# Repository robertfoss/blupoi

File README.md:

blupoi
======

TODO
----

Changes since v0.3:
 - 1uF 0402 caps not ordered
 * C27 pad has a large via in a pad
 * FIXED: MAX16054 Connect CLEAR to GND if unused.
 * FIXED: SIP32408 Footprint pinout was mirrored
 ? Change battery orientation, since spring should be on the top side but also on the gnd side of BAT
  - Maybe dont since VBAT would end up coming out in a place where it is not useful
 * X1 label covered by hole
 * X1 footprint larger than bom part?
 * C1/C2/C3 footprint is 0603 but bom is 0402
 * SWO header, change part and footprint to have only be connectable the 'right' way

Changes since v0.2:
 * FIXED: Replaced USB connector oval holes with round ones for improved fabricability
 * FIXED: Reflowed filled zones since KiCad somehow did it randomly wrong in v0.2
 * FIXED: R1 Move via further away from pad
 * FIXED: Move USB connector and power button to the side

Changes since v0.1:
 * FIXED: Battery compartment is not quite wide enough.
 * IGNORE: Battery compartment battery spring slot is:
   - 0.5mm too thin, should be 1.6mm
   - 0.5mm too slim, should me 17.75mm
 * FIXED: Spring slots lack copper on the back side
 * FIXED: +/- symbols on the battery silkscreen
 ? IGNORE: battery footprint 180 degrees

 * FIXED: U5/bq24075 EN1 is not pulled down
 * FIXED: U5/bq24075 sysoff turns charging off. Which is should never dd
   - Add separate add some kind of switch between u5 out and vin, controlled by button logic
   - Pull sysoff down
 * Add Load switch like Sip32431 - http://www.vishay.com/docs/66597/sip32431.pdf
   - But ~4.8A at @ 5V
   - SiP32101? No. Is LGA package
   - SiP32408? 3.5A probably ok since no usb port delivers that, and probable no battery either
     - http://www.vishay.com/docs/63717/sip32408.pdf

 * FIXED: Mic port hole is not drilled (hole too small?)
 * FIXED: Mic pads should probably be longer

 * FIXED: Move button footprint slightly closer to edge

 * FIXED: BNO055 pads should probable be longer

 * FIXED: Make logos bigger to make details visible

 * FIXED: Change L2 footprint from 0603 to 1206

 * Vin not connected on 3.3V regulator

 * FIXED: Add silkscreen saying:
   look at you, hacker, a pathetic creature of meat and bone. how can you compare yourself to a perfect immortal machine.

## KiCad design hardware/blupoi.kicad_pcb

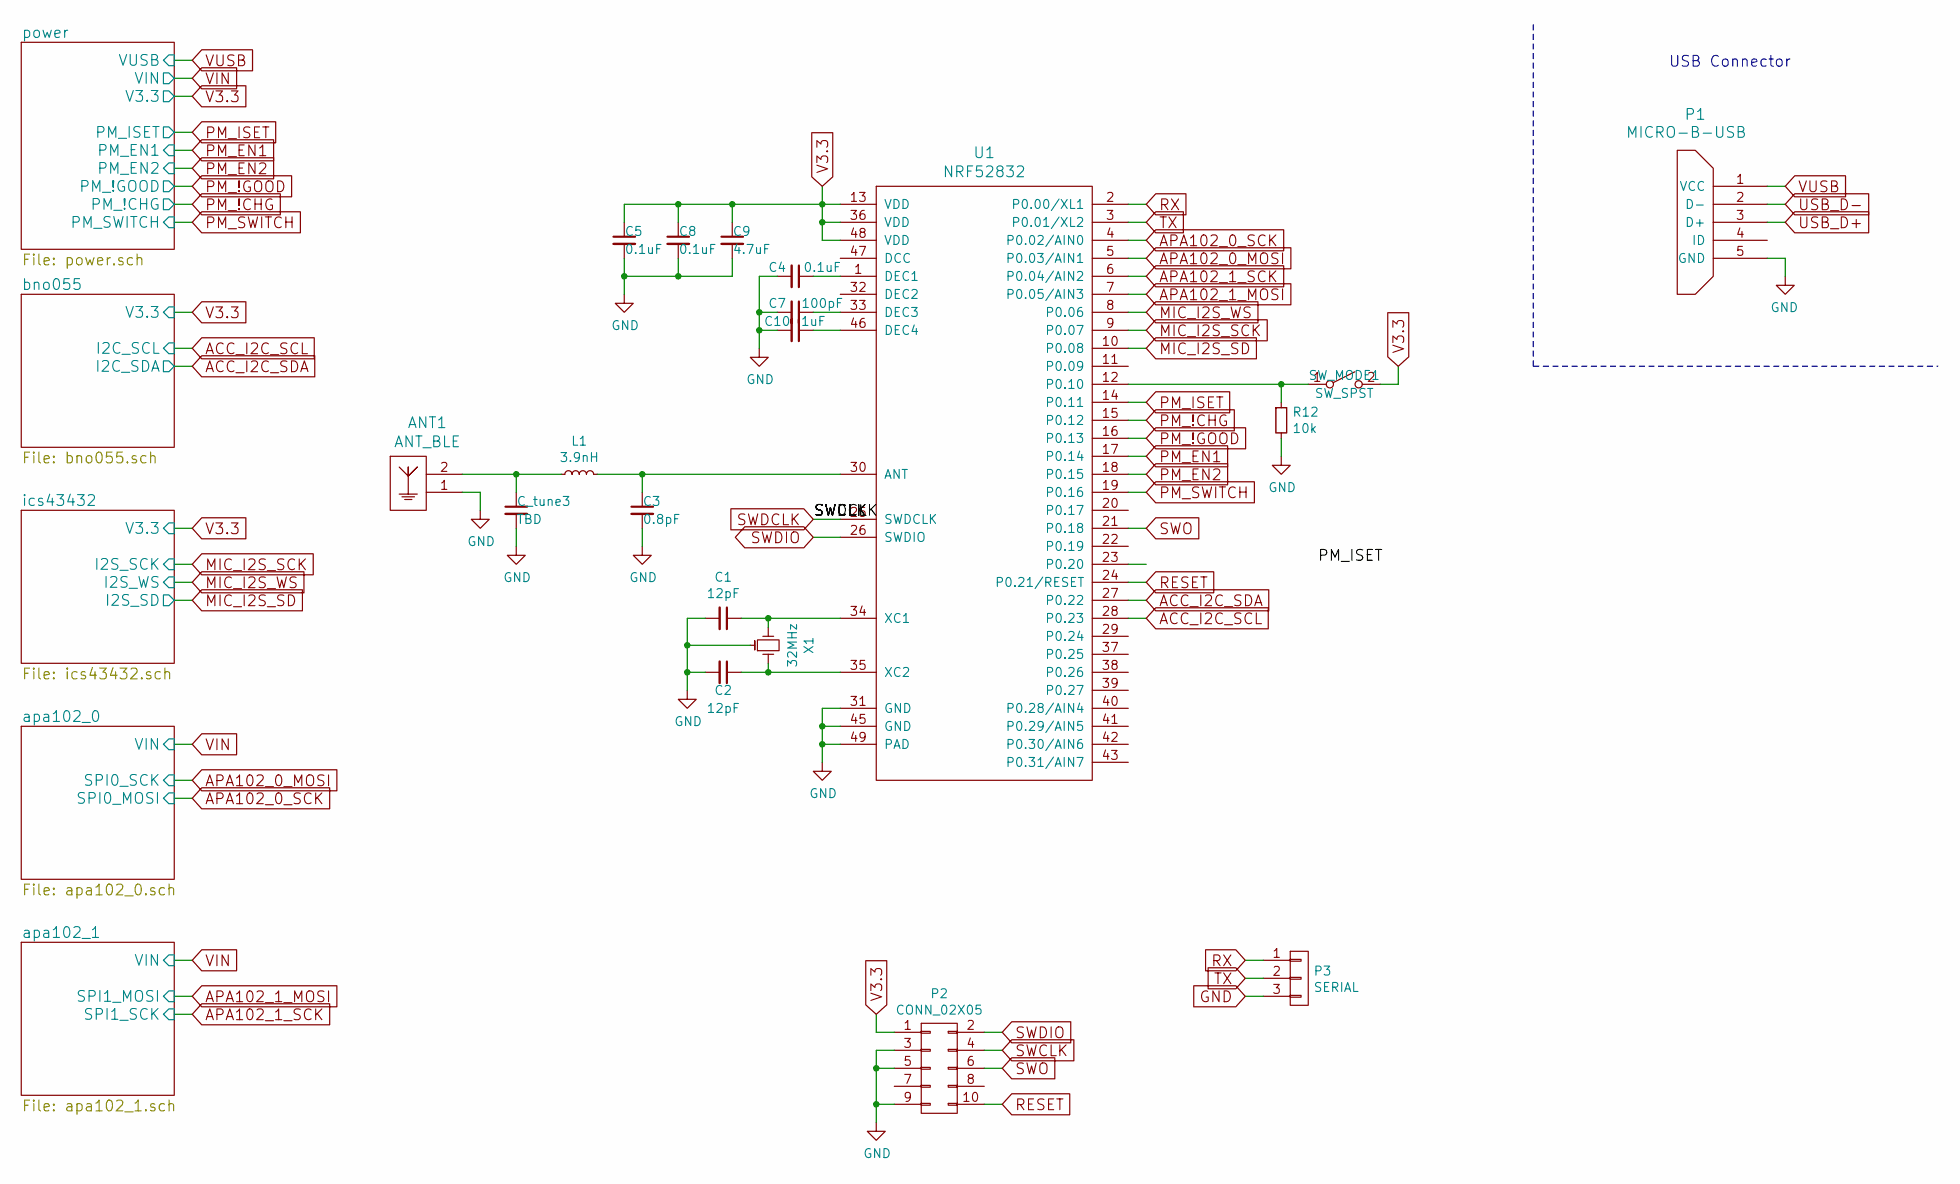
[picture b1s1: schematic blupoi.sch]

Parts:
ANT1: ANT_BLE; ti-an043-antenna
C1, C2: 12pF; C_0402
C3: 0.8pF; C_0402; MFG Part Num Value
C4: 0.1uF; C_0402
C5, C8: 0.1uF; C_0402; MFG Part Num Value
C7: 100pF; C_0402; MFG Part Num Value
C9: 4.7uF; C_0603; MFG Part Num Value
C10: 1uF; C_0603; MFG Part Num Value
C_tune3: TBD; C_0603_HandSoldering; MFG Part Num Value
L1: 3.9nH; C_0402
P1: MICRO-B-USB; USB_Micro-B
P2: CONN_02X05; Pin_Header_Straight_2x05
P3: SERIAL; Pin_Header_Straight_1x03
R12: 10k; R_0603
SW_MODE1: SW_SPST; KSS241GLFS
U1: NRF52832; UQFN-48-1EP_6x6mm_Pitch0.4mm
X1: 32MHz; XTAL2016; MFG Part Num Value

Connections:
ACC_I2C_SCL: U1.28 (P0.23); also elsewhere on the board
ACC_I2C_SDA: U1.27 (P0.22); also elsewhere on the board
APA102_0_MOSI: U1.5 (P0.03/AIN1); also elsewhere on the board
APA102_0_SCK: U1.4 (P0.02/AIN0); also elsewhere on the board
APA102_1_MOSI: U1.7 (P0.05/AIN3); also elsewhere on the board
APA102_1_SCK: U1.6 (P0.04/AIN2); also elsewhere on the board
GND: ANT1.1, C1.2, C2.2, C3.2, C4.2, C5.2, C7.2, C8.2, C9.2, C10.2, C_tune3.2, P1.5 (GND), P2.3, P2.5, P2.9, R12.2, U1.31 (GND), U1.45 (GND), U1.49 (PAD), X1.3; also elsewhere on the board
MIC_I2S_SCK: U1.9 (P0.07); also elsewhere on the board
MIC_I2S_SD: U1.10 (P0.08); also elsewhere on the board
MIC_I2S_WS: U1.8 (P0.06); also elsewhere on the board
unnamed: ANT1.2, C_tune3.1, L1.1
unnamed: C1.1, U1.34 (XC1), X1.2
unnamed: C2.1, U1.35 (XC2), X1.1
unnamed: C3.1, L1.2, U1.30 (ANT)
unnamed: C4.1, U1.1 (DEC1)
unnamed: C7.1, U1.33 (DEC3)
unnamed: C10.1, U1.46 (DEC4)
unnamed: R12.1, SW_MODE1.1 (A), U1.12 (P0.10)
PM_!CHG: U1.15 (P0.12); also elsewhere on the board
PM_!GOOD: U1.16 (P0.13); also elsewhere on the board
PM_EN1: U1.17 (P0.14); also elsewhere on the board
PM_EN2: U1.18 (P0.15); also elsewhere on the board
PM_ISET: U1.14 (P0.11); also elsewhere on the board
PM_SWITCH: U1.19 (P0.16); also elsewhere on the board
RESET: P2.10, U1.24 (P0.21/RESET); also elsewhere on the board
RX: P3.1, U1.2 (P0.00/XL1); also elsewhere on the board
SWCLK: U1.25 (SWDCLK); also elsewhere on the board
SWDIO: P2.2, U1.26 (SWDIO); also elsewhere on the board
SWO: P2.6, U1.21 (P0.18); also elsewhere on the board
TX: P3.2, U1.3 (P0.01/XL2); also elsewhere on the board
USB_D+: P1.3 (D+)
USB_D-: P1.2 (D-)
V3.3: C5.1, C8.1, C9.1, P2.1, SW_MODE1.2 (B), U1.13 (VDD), U1.36 (VDD), U1.48 (VDD); also elsewhere on the board
VUSB: P1.1 (VCC); also elsewhere on the board

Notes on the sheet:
USB Connector

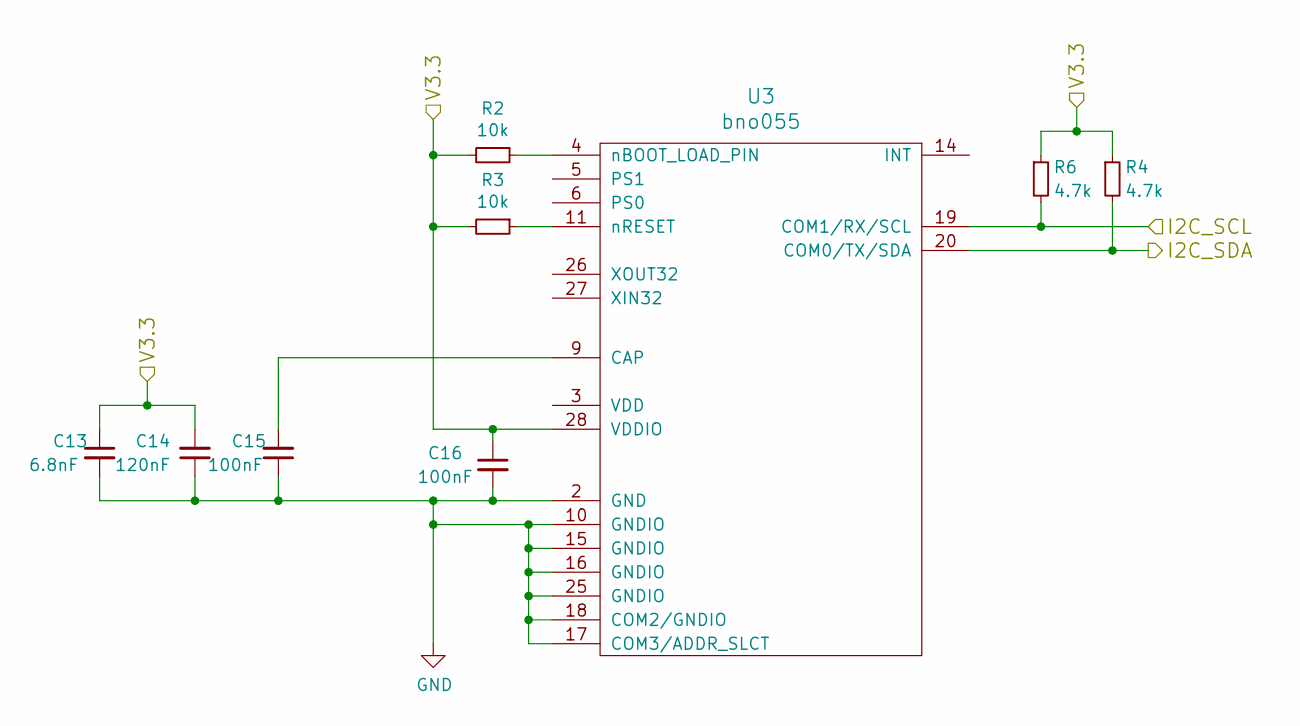
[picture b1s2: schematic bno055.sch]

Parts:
C13: 6.8nF; C_0402
C14: 120nF; C_0402
C15, C16: 100nF; C_0402
R2, R3: 10k; R_0603
R4, R6: 4.7k; R_0603
U3: bno055

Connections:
ACC_I2C_SCL: R6.2, U3.19 (COM1/RX/SCL); also elsewhere on the board
ACC_I2C_SDA: R4.2, U3.20 (COM0/TX/SDA); also elsewhere on the board
GND: C13.2, C14.1, C15.1, C16.2, U3.2 (GND), U3.10 (GNDIO), U3.15 (GNDIO), U3.16 (GNDIO), U3.17 (COM3/ADDR_SLCT), U3.18 (COM2/GNDIO), U3.25 (GNDIO); also elsewhere on the board
unnamed: C15.2, U3.9 (CAP)
unnamed: R2.1, U3.4 (nBOOT_LOAD_PIN)
unnamed: R3.1, U3.11 (nRESET)
V3.3: C13.1, C14.2, C16.1, R2.2, R3.2, R4.1, R6.1, U3.28 (VDDIO); also elsewhere on the board

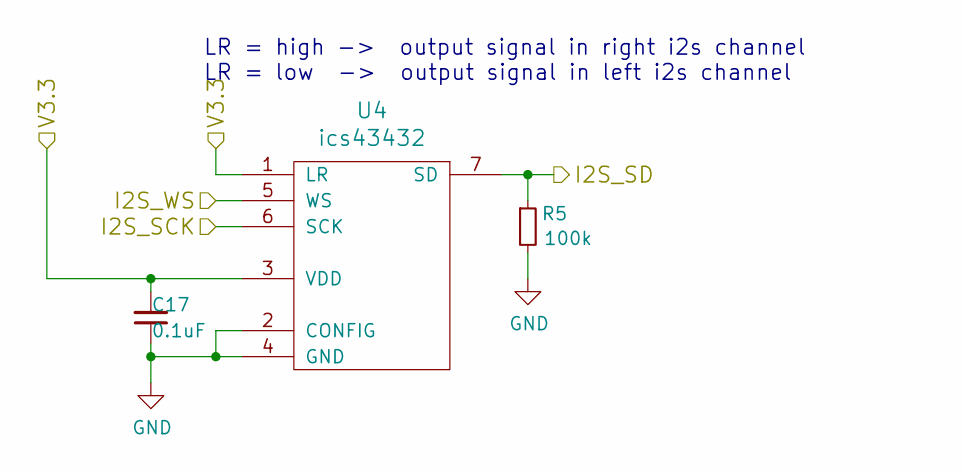
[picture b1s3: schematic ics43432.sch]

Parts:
C17: 0.1uF; C_0402
R5: 100k; R_0603
U4: ics43432

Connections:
GND: C17.1, R5.2, U4.2 (CONFIG), U4.4 (GND); also elsewhere on the board
MIC_I2S_SCK: U4.6 (SCK); also elsewhere on the board
MIC_I2S_SD: R5.1, U4.7 (SD); also elsewhere on the board
MIC_I2S_WS: U4.5 (WS); also elsewhere on the board
V3.3: C17.2, U4.1 (LR), U4.3 (VDD); also elsewhere on the board

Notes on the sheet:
LR = high -> output signal in right i2s channel LR = low -> output signal in left i2s channel

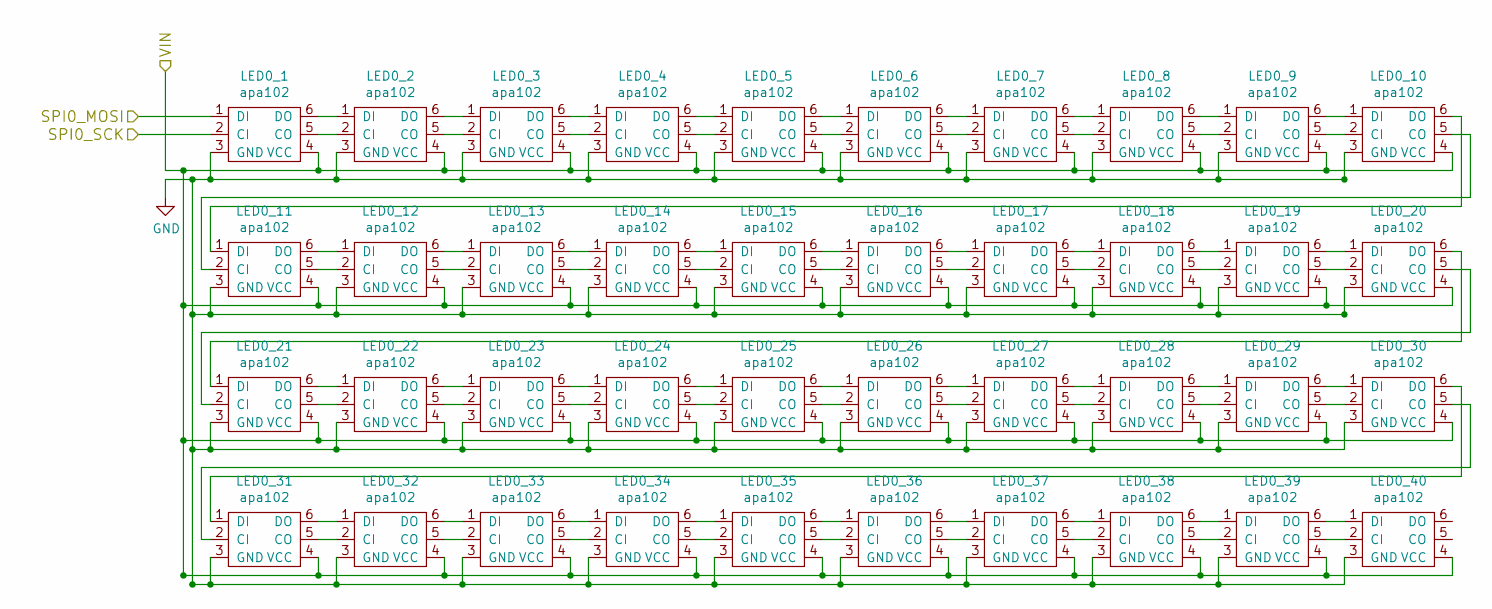
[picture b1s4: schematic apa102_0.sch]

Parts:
LED0_1, LED0_2, LED0_3, LED0_4, LED0_5, LED0_6, LED0_7, LED0_8, LED0_9, LED0_10, LED0_11, LED0_12, LED0_13, LED0_14, LED0_15, LED0_16, LED0_17, LED0_18, LED0_19, LED0_20, LED0_21, LED0_22, LED0_23, LED0_24, LED0_25, LED0_26, LED0_27, LED0_28, LED0_29, LED0_30, LED0_31, LED0_32, LED0_33, LED0_34, LED0_35, LED0_36, LED0_37, LED0_38, LED0_39, LED0_40: apa102

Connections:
APA102_0_MOSI: LED0_1.2 (CI); also elsewhere on the board
APA102_0_SCK: LED0_1.1 (DI); also elsewhere on the board
GND: LED0_1.3 (GND), LED0_2.3 (GND), LED0_3.3 (GND), LED0_4.3 (GND), LED0_5.3 (GND), LED0_6.3 (GND), LED0_7.3 (GND), LED0_8.3 (GND), LED0_9.3 (GND), LED0_10.3 (GND), LED0_11.3 (GND), LED0_12.3 (GND), LED0_13.3 (GND), LED0_14.3 (GND), LED0_15.3 (GND), LED0_16.3 (GND), LED0_17.3 (GND), LED0_18.3 (GND), LED0_19.3 (GND), LED0_20.3 (GND), LED0_21.3 (GND), LED0_22.3 (GND), LED0_23.3 (GND), LED0_24.3 (GND), LED0_25.3 (GND), LED0_26.3 (GND), LED0_27.3 (GND), LED0_28.3 (GND), LED0_29.3 (GND), LED0_30.3 (GND), LED0_31.3 (GND), LED0_32.3 (GND), LED0_33.3 (GND), LED0_34.3 (GND), LED0_35.3 (GND), LED0_36.3 (GND), LED0_37.3 (GND), LED0_38.3 (GND), LED0_39.3 (GND), LED0_40.3 (GND); also elsewhere on the board
unnamed: LED0_1.5 (CO), LED0_2.2 (CI)
unnamed: LED0_1.6 (DO), LED0_2.1 (DI)
unnamed: LED0_2.5 (CO), LED0_3.2 (CI)
unnamed: LED0_2.6 (DO), LED0_3.1 (DI)
unnamed: LED0_3.5 (CO), LED0_4.2 (CI)
unnamed: LED0_3.6 (DO), LED0_4.1 (DI)
unnamed: LED0_4.5 (CO), LED0_5.2 (CI)
unnamed: LED0_4.6 (DO), LED0_5.1 (DI)
unnamed: LED0_5.5 (CO), LED0_6.2 (CI)
unnamed: LED0_5.6 (DO), LED0_6.1 (DI)
unnamed: LED0_6.5 (CO), LED0_7.2 (CI)
unnamed: LED0_6.6 (DO), LED0_7.1 (DI)
unnamed: LED0_7.5 (CO), LED0_8.2 (CI)
unnamed: LED0_7.6 (DO), LED0_8.1 (DI)
unnamed: LED0_8.5 (CO), LED0_9.2 (CI)
unnamed: LED0_8.6 (DO), LED0_9.1 (DI)
unnamed: LED0_9.6 (DO), LED0_10.1 (DI)
unnamed: LED0_9.5 (CO), LED0_10.2 (CI)
unnamed: LED0_10.5 (CO), LED0_11.2 (CI)
unnamed: LED0_10.6 (DO), LED0_11.1 (DI)
unnamed: LED0_11.5 (CO), LED0_12.2 (CI)
unnamed: LED0_11.6 (DO), LED0_12.1 (DI)
unnamed: LED0_12.5 (CO), LED0_13.2 (CI)
unnamed: LED0_12.6 (DO), LED0_13.1 (DI)
unnamed: LED0_13.5 (CO), LED0_14.2 (CI)
unnamed: LED0_13.6 (DO), LED0_14.1 (DI)
unnamed: LED0_14.5 (CO), LED0_15.2 (CI)
unnamed: LED0_14.6 (DO), LED0_15.1 (DI)
unnamed: LED0_15.5 (CO), LED0_16.2 (CI)
unnamed: LED0_15.6 (DO), LED0_16.1 (DI)
unnamed: LED0_16.5 (CO), LED0_17.2 (CI)
unnamed: LED0_16.6 (DO), LED0_17.1 (DI)
unnamed: LED0_17.5 (CO), LED0_18.2 (CI)
unnamed: LED0_17.6 (DO), LED0_18.1 (DI)
unnamed: LED0_18.5 (CO), LED0_19.2 (CI)
unnamed: LED0_18.6 (DO), LED0_19.1 (DI)
unnamed: LED0_19.5 (CO), LED0_20.2 (CI)
unnamed: LED0_19.6 (DO), LED0_20.1 (DI)
unnamed: LED0_20.5 (CO), LED0_21.2 (CI)
unnamed: LED0_20.6 (DO), LED0_21.1 (DI)
unnamed: LED0_21.5 (CO), LED0_22.2 (CI)
unnamed: LED0_21.6 (DO), LED0_22.1 (DI)
unnamed: LED0_22.5 (CO), LED0_23.2 (CI)
unnamed: LED0_22.6 (DO), LED0_23.1 (DI)
unnamed: LED0_23.5 (CO), LED0_24.2 (CI)
unnamed: LED0_23.6 (DO), LED0_24.1 (DI)
unnamed: LED0_24.5 (CO), LED0_25.2 (CI)
unnamed: LED0_24.6 (DO), LED0_25.1 (DI)
unnamed: LED0_25.5 (CO), LED0_26.2 (CI)
unnamed: LED0_25.6 (DO), LED0_26.1 (DI)
unnamed: LED0_26.5 (CO), LED0_27.2 (CI)
unnamed: LED0_26.6 (DO), LED0_27.1 (DI)
unnamed: LED0_27.5 (CO), LED0_28.2 (CI)
unnamed: LED0_27.6 (DO), LED0_28.1 (DI)
unnamed: LED0_28.5 (CO), LED0_29.2 (CI)
unnamed: LED0_28.6 (DO), LED0_29.1 (DI)
unnamed: LED0_29.5 (CO), LED0_30.2 (CI)
unnamed: LED0_29.6 (DO), LED0_30.1 (DI)
unnamed: LED0_30.5 (CO), LED0_31.2 (CI)
unnamed: LED0_30.6 (DO), LED0_31.1 (DI)
unnamed: LED0_31.5 (CO), LED0_32.2 (CI)
unnamed: LED0_31.6 (DO), LED0_32.1 (DI)
unnamed: LED0_32.5 (CO), LED0_33.2 (CI)
unnamed: LED0_32.6 (DO), LED0_33.1 (DI)
unnamed: LED0_33.5 (CO), LED0_34.2 (CI)
unnamed: LED0_33.6 (DO), LED0_34.1 (DI)
unnamed: LED0_34.5 (CO), LED0_35.2 (CI)
unnamed: LED0_34.6 (DO), LED0_35.1 (DI)
unnamed: LED0_35.5 (CO), LED0_36.2 (CI)
unnamed: LED0_35.6 (DO), LED0_36.1 (DI)
unnamed: LED0_36.5 (CO), LED0_37.2 (CI)
unnamed: LED0_36.6 (DO), LED0_37.1 (DI)
unnamed: LED0_37.5 (CO), LED0_38.2 (CI)
unnamed: LED0_37.6 (DO), LED0_38.1 (DI)
unnamed: LED0_38.5 (CO), LED0_39.2 (CI)
unnamed: LED0_38.6 (DO), LED0_39.1 (DI)
unnamed: LED0_39.5 (CO), LED0_40.2 (CI)
unnamed: LED0_39.6 (DO), LED0_40.1 (DI)
VIN: LED0_1.4 (VCC), LED0_2.4 (VCC), LED0_3.4 (VCC), LED0_4.4 (VCC), LED0_5.4 (VCC), LED0_6.4 (VCC), LED0_7.4 (VCC), LED0_8.4 (VCC), LED0_9.4 (VCC), LED0_10.4 (VCC), LED0_11.4 (VCC), LED0_12.4 (VCC), LED0_13.4 (VCC), LED0_14.4 (VCC), LED0_15.4 (VCC), LED0_16.4 (VCC), LED0_17.4 (VCC), LED0_18.4 (VCC), LED0_19.4 (VCC), LED0_20.4 (VCC), LED0_21.4 (VCC), LED0_22.4 (VCC), LED0_23.4 (VCC), LED0_24.4 (VCC), LED0_25.4 (VCC), LED0_26.4 (VCC), LED0_27.4 (VCC), LED0_28.4 (VCC), LED0_29.4 (VCC), LED0_30.4 (VCC), LED0_31.4 (VCC), LED0_32.4 (VCC), LED0_33.4 (VCC), LED0_34.4 (VCC), LED0_35.4 (VCC), LED0_36.4 (VCC), LED0_37.4 (VCC), LED0_38.4 (VCC), LED0_39.4 (VCC), LED0_40.4 (VCC); also elsewhere on the board

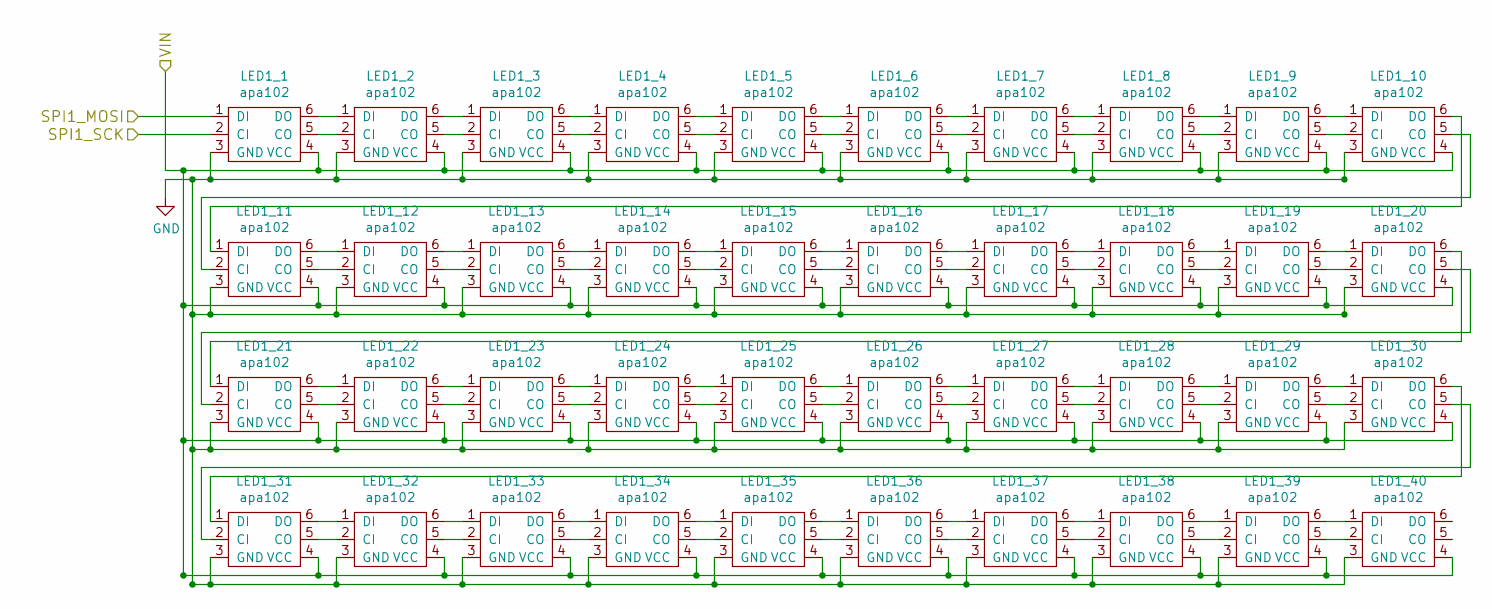
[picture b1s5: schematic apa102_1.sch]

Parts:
LED1_1, LED1_2, LED1_3, LED1_4, LED1_5, LED1_6, LED1_7, LED1_8, LED1_9, LED1_10, LED1_11, LED1_12, LED1_13, LED1_14, LED1_15, LED1_16, LED1_17, LED1_18, LED1_19, LED1_20, LED1_21, LED1_22, LED1_23, LED1_24, LED1_25, LED1_26, LED1_27, LED1_28, LED1_29, LED1_30, LED1_31, LED1_32, LED1_33, LED1_34, LED1_35, LED1_36, LED1_37, LED1_38, LED1_39, LED1_40: apa102

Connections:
APA102_1_MOSI: LED1_1.1 (DI); also elsewhere on the board
APA102_1_SCK: LED1_1.2 (CI); also elsewhere on the board
GND: LED1_1.3 (GND), LED1_2.3 (GND), LED1_3.3 (GND), LED1_4.3 (GND), LED1_5.3 (GND), LED1_6.3 (GND), LED1_7.3 (GND), LED1_8.3 (GND), LED1_9.3 (GND), LED1_10.3 (GND), LED1_11.3 (GND), LED1_12.3 (GND), LED1_13.3 (GND), LED1_14.3 (GND), LED1_15.3 (GND), LED1_16.3 (GND), LED1_17.3 (GND), LED1_18.3 (GND), LED1_19.3 (GND), LED1_20.3 (GND), LED1_21.3 (GND), LED1_22.3 (GND), LED1_23.3 (GND), LED1_24.3 (GND), LED1_25.3 (GND), LED1_26.3 (GND), LED1_27.3 (GND), LED1_28.3 (GND), LED1_29.3 (GND), LED1_30.3 (GND), LED1_31.3 (GND), LED1_32.3 (GND), LED1_33.3 (GND), LED1_34.3 (GND), LED1_35.3 (GND), LED1_36.3 (GND), LED1_37.3 (GND), LED1_38.3 (GND), LED1_39.3 (GND), LED1_40.3 (GND); also elsewhere on the board
unnamed: LED1_1.5 (CO), LED1_2.2 (CI)
unnamed: LED1_1.6 (DO), LED1_2.1 (DI)
unnamed: LED1_2.5 (CO), LED1_3.2 (CI)
unnamed: LED1_2.6 (DO), LED1_3.1 (DI)
unnamed: LED1_3.5 (CO), LED1_4.2 (CI)
unnamed: LED1_3.6 (DO), LED1_4.1 (DI)
unnamed: LED1_4.5 (CO), LED1_5.2 (CI)
unnamed: LED1_4.6 (DO), LED1_5.1 (DI)
unnamed: LED1_5.5 (CO), LED1_6.2 (CI)
unnamed: LED1_5.6 (DO), LED1_6.1 (DI)
unnamed: LED1_6.5 (CO), LED1_7.2 (CI)
unnamed: LED1_6.6 (DO), LED1_7.1 (DI)
unnamed: LED1_7.5 (CO), LED1_8.2 (CI)
unnamed: LED1_7.6 (DO), LED1_8.1 (DI)
unnamed: LED1_8.5 (CO), LED1_9.2 (CI)
unnamed: LED1_8.6 (DO), LED1_9.1 (DI)
unnamed: LED1_9.6 (DO), LED1_10.1 (DI)
unnamed: LED1_9.5 (CO), LED1_10.2 (CI)
unnamed: LED1_10.5 (CO), LED1_11.2 (CI)
unnamed: LED1_10.6 (DO), LED1_11.1 (DI)
unnamed: LED1_11.5 (CO), LED1_12.2 (CI)
unnamed: LED1_11.6 (DO), LED1_12.1 (DI)
unnamed: LED1_12.5 (CO), LED1_13.2 (CI)
unnamed: LED1_12.6 (DO), LED1_13.1 (DI)
unnamed: LED1_13.5 (CO), LED1_14.2 (CI)
unnamed: LED1_13.6 (DO), LED1_14.1 (DI)
unnamed: LED1_14.5 (CO), LED1_15.2 (CI)
unnamed: LED1_14.6 (DO), LED1_15.1 (DI)
unnamed: LED1_15.5 (CO), LED1_16.2 (CI)
unnamed: LED1_15.6 (DO), LED1_16.1 (DI)
unnamed: LED1_16.5 (CO), LED1_17.2 (CI)
unnamed: LED1_16.6 (DO), LED1_17.1 (DI)
unnamed: LED1_17.5 (CO), LED1_18.2 (CI)
unnamed: LED1_17.6 (DO), LED1_18.1 (DI)
unnamed: LED1_18.5 (CO), LED1_19.2 (CI)
unnamed: LED1_18.6 (DO), LED1_19.1 (DI)
unnamed: LED1_19.5 (CO), LED1_20.2 (CI)
unnamed: LED1_19.6 (DO), LED1_20.1 (DI)
unnamed: LED1_20.5 (CO), LED1_21.2 (CI)
unnamed: LED1_20.6 (DO), LED1_21.1 (DI)
unnamed: LED1_21.5 (CO), LED1_22.2 (CI)
unnamed: LED1_21.6 (DO), LED1_22.1 (DI)
unnamed: LED1_22.5 (CO), LED1_23.2 (CI)
unnamed: LED1_22.6 (DO), LED1_23.1 (DI)
unnamed: LED1_23.5 (CO), LED1_24.2 (CI)
unnamed: LED1_23.6 (DO), LED1_24.1 (DI)
unnamed: LED1_24.5 (CO), LED1_25.2 (CI)
unnamed: LED1_24.6 (DO), LED1_25.1 (DI)
unnamed: LED1_25.5 (CO), LED1_26.2 (CI)
unnamed: LED1_25.6 (DO), LED1_26.1 (DI)
unnamed: LED1_26.5 (CO), LED1_27.2 (CI)
unnamed: LED1_26.6 (DO), LED1_27.1 (DI)
unnamed: LED1_27.5 (CO), LED1_28.2 (CI)
unnamed: LED1_27.6 (DO), LED1_28.1 (DI)
unnamed: LED1_28.5 (CO), LED1_29.2 (CI)
unnamed: LED1_28.6 (DO), LED1_29.1 (DI)
unnamed: LED1_29.5 (CO), LED1_30.2 (CI)
unnamed: LED1_29.6 (DO), LED1_30.1 (DI)
unnamed: LED1_30.5 (CO), LED1_31.2 (CI)
unnamed: LED1_30.6 (DO), LED1_31.1 (DI)
unnamed: LED1_31.5 (CO), LED1_32.2 (CI)
unnamed: LED1_31.6 (DO), LED1_32.1 (DI)
unnamed: LED1_32.5 (CO), LED1_33.2 (CI)
unnamed: LED1_32.6 (DO), LED1_33.1 (DI)
unnamed: LED1_33.5 (CO), LED1_34.2 (CI)
unnamed: LED1_33.6 (DO), LED1_34.1 (DI)
unnamed: LED1_34.5 (CO), LED1_35.2 (CI)
unnamed: LED1_34.6 (DO), LED1_35.1 (DI)
unnamed: LED1_35.5 (CO), LED1_36.2 (CI)
unnamed: LED1_35.6 (DO), LED1_36.1 (DI)
unnamed: LED1_36.5 (CO), LED1_37.2 (CI)
unnamed: LED1_36.6 (DO), LED1_37.1 (DI)
unnamed: LED1_37.5 (CO), LED1_38.2 (CI)
unnamed: LED1_37.6 (DO), LED1_38.1 (DI)
unnamed: LED1_38.5 (CO), LED1_39.2 (CI)
unnamed: LED1_38.6 (DO), LED1_39.1 (DI)
unnamed: LED1_39.5 (CO), LED1_40.2 (CI)
unnamed: LED1_39.6 (DO), LED1_40.1 (DI)
VIN: LED1_1.4 (VCC), LED1_2.4 (VCC), LED1_3.4 (VCC), LED1_4.4 (VCC), LED1_5.4 (VCC), LED1_6.4 (VCC), LED1_7.4 (VCC), LED1_8.4 (VCC), LED1_9.4 (VCC), LED1_10.4 (VCC), LED1_11.4 (VCC), LED1_12.4 (VCC), LED1_13.4 (VCC), LED1_14.4 (VCC), LED1_15.4 (VCC), LED1_16.4 (VCC), LED1_17.4 (VCC), LED1_18.4 (VCC), LED1_19.4 (VCC), LED1_20.4 (VCC), LED1_21.4 (VCC), LED1_22.4 (VCC), LED1_23.4 (VCC), LED1_24.4 (VCC), LED1_25.4 (VCC), LED1_26.4 (VCC), LED1_27.4 (VCC), LED1_28.4 (VCC), LED1_29.4 (VCC), LED1_30.4 (VCC), LED1_31.4 (VCC), LED1_32.4 (VCC), LED1_33.4 (VCC), LED1_34.4 (VCC), LED1_35.4 (VCC), LED1_36.4 (VCC), LED1_37.4 (VCC), LED1_38.4 (VCC), LED1_39.4 (VCC), LED1_40.4 (VCC); also elsewhere on the board

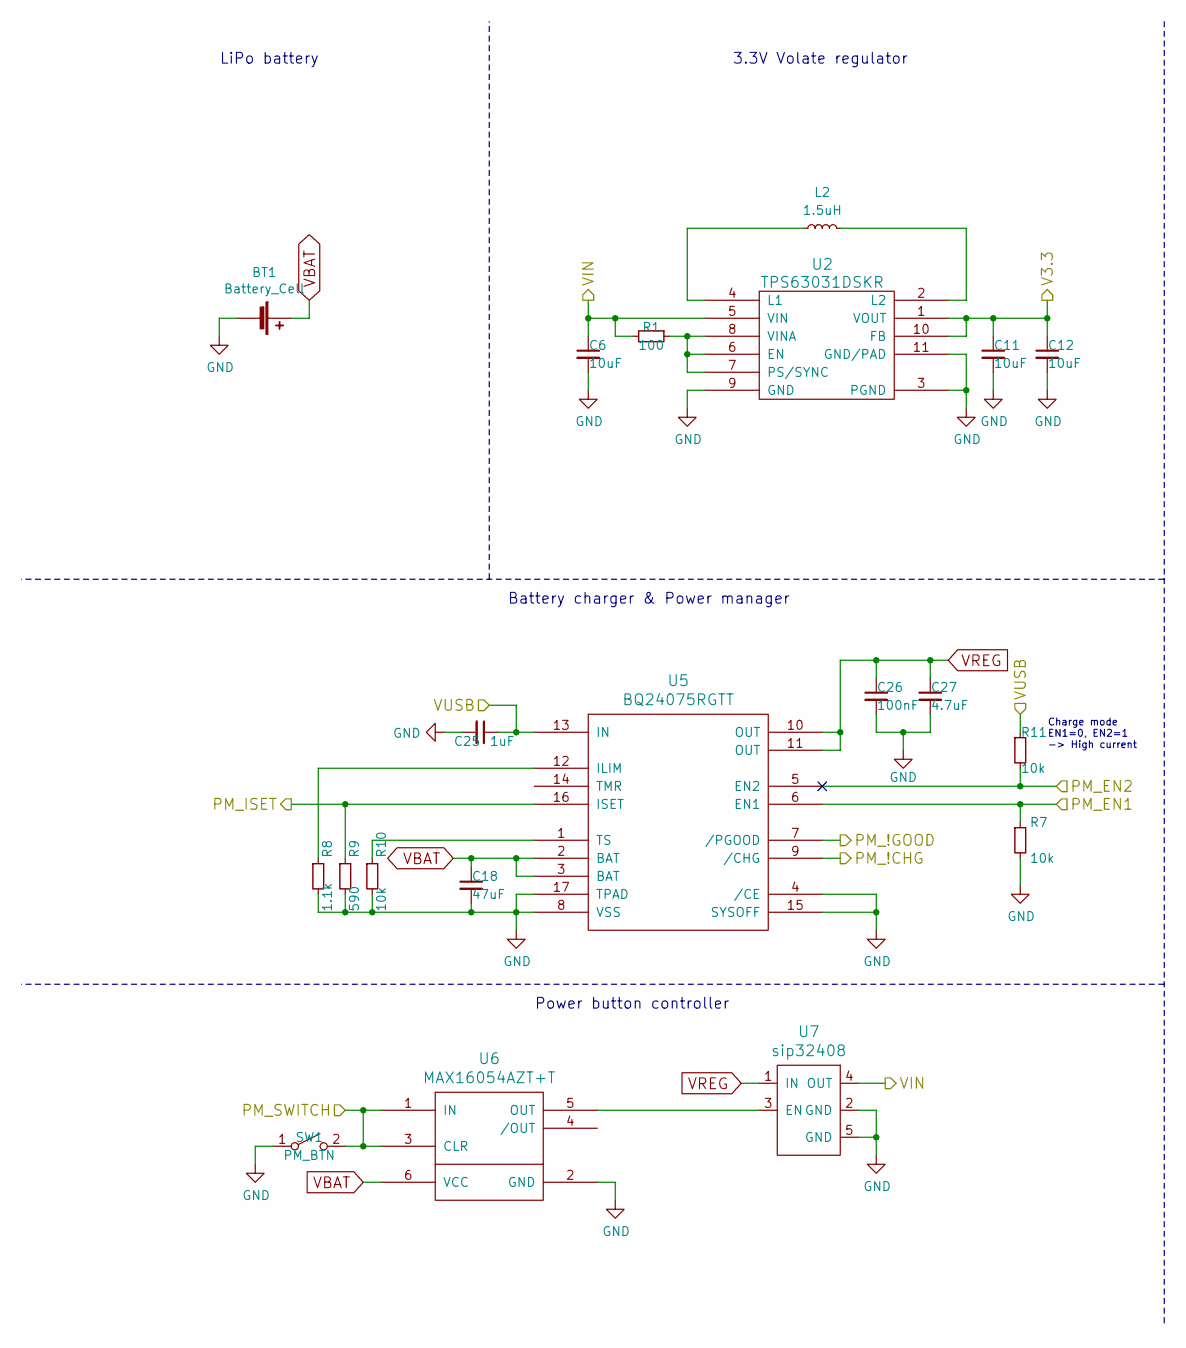
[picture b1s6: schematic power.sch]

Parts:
BT1: Battery_Cell; 16650_in_pcb_socket
C6, C11, C12: 10uF; C_0603
C18: 47uF; C_0805
C25: 1uF; C_0402
C26: 100nF; C_0402
C27: 4.7uF; C_0402
L2: 1.5uH; R_1206
R1: 100; R_0603
R7, R10, R11: 10k; R_0603
R8: 1.1k; R_0603
R9: 590; R_0603
SW1: PM_BTN; KSS241GLFS
U2: TPS63031DSKR; VSON-10
U5: BQ24075RGTT; QFN-16-1EP_3x3mm_Pitch0.5mm
U6: MAX16054AZT+T; SOT23-6
U7: sip32408

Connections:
GND: BT1.2 (-), C6.2, C11.2, C12.2, C18.2, C25.2, C26.2, C27.2, R7.2, R8.2, R9.2, R10.2, SW1.1 (A), U2.3 (PGND), U2.9 (GND), U2.11 (GND/PAD), U5.4 (/CE), U5.8 (VSS), U5.15 (SYSOFF), U5.17 (TPAD), U6.2 (GND), U7.2 (GND), U7.5 (GND); also elsewhere on the board
unnamed: L2.1, U2.4 (L1)
unnamed: L2.2, U2.2 (L2)
unnamed: R1.1, U2.6 (EN), U2.7 (PS/SYNC), U2.8 (VINA)
unnamed: R8.1, U5.12 (ILIM)
unnamed: R10.1, U5.1 (TS)
unnamed: U6.5 (OUT), U7.3 (EN)
PM_!CHG: U5.9 (/CHG); also elsewhere on the board
PM_!GOOD: U5.7 (/PGOOD); also elsewhere on the board
PM_EN1: R7.1, U5.6 (EN1); also elsewhere on the board
PM_EN2: R11.2, U5.5 (EN2); also elsewhere on the board
PM_ISET: R9.1, U5.16 (ISET); also elsewhere on the board
PM_SWITCH: SW1.2 (B), U6.1 (IN), U6.3 (CLR); also elsewhere on the board
V3.3: C11.1, C12.1, U2.1 (VOUT), U2.10 (FB); also elsewhere on the board
VBAT: BT1.1 (+), C18.1, U5.2 (BAT), U5.3 (BAT), U6.6 (VCC)
VIN: C6.1, R1.2, U2.5 (VIN), U7.4 (OUT); also elsewhere on the board
VREG: C26.1, C27.1, U5.10 (OUT), U5.11 (OUT), U7.1 (IN)
VUSB: C25.1, R11.1, U5.13 (IN); also elsewhere on the board

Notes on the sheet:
LiPo battery
3.3V Volate regulator
Power button controller
Battery charger & Power manager
Charge mode EN1=0, EN2=1 -> High current

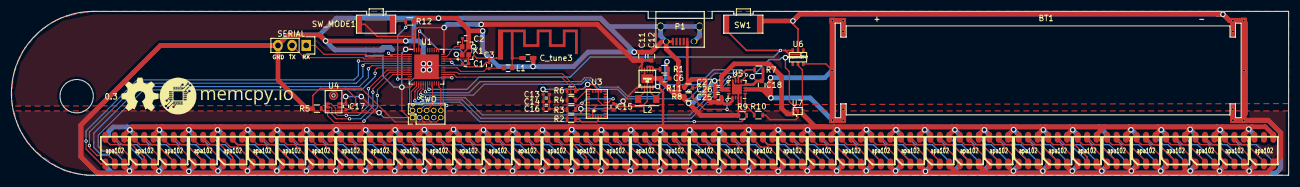
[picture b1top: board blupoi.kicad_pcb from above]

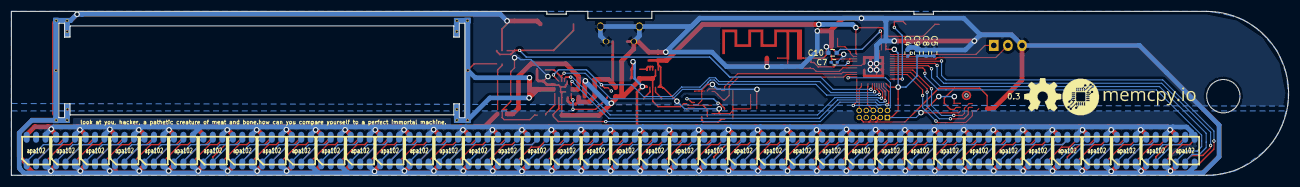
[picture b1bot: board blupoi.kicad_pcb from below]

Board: 2 copper layers, 229.7 x 29.4 mm, 131 parts (46 on the bottom side), 200 nets.

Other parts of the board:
SERIAL: SERIAL; Pin_Header_Straight_1x03
SWO: CONN_02X05; Pin_Header_Straight_2x05_Pitch1.27mm

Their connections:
GND: SERIAL.3, SWO.3, SWO.5, SWO.9; also elsewhere on the board
RESET: SWO.10; also elsewhere on the board
RX: SERIAL.1; also elsewhere on the board
SWCLK: SWO.4; also elsewhere on the board
SWDIO: SWO.2; also elsewhere on the board
SWO: SWO.6; also elsewhere on the board
TX: SERIAL.2; also elsewhere on the board
V3.3: SWO.1; also elsewhere on the board

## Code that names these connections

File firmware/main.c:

#include <stdlib.h>

#include "apa102.h"
#include "uart.h"


const uint32_t apa102_0_sck = 2;
const uint32_t apa102_0_mosi = 3;
const uint32_t apa102_1_sck = 4;
const uint32_t apa102_1_mosi = 5;
const uint32_t apa102_nbr_leds = 40;
apa102_t *apa102_0;
apa102_t *apa102_1;


void app_error_fault_handler(uint32_t id, uint32_t pc, uint32_t info)
{
    #ifdef DEBUG
    app_error_print(id, pc, info);
    #endif

    apa102_led_t red = { .a = 32, .r = 255, .g = 0, .b = 0 };
    apa102_setcolor(apa102_0, &red);
    apa102_setcolor(apa102_1, &red);

    while (1);
}

int main(void) {

    /* Setup */
    uart_init(2, 3, 256);
    uart_send("uart_init complete\r\n");
    printf("printf: uart_init complete\r\n");
    apa102_0 = apa102_init(apa102_nbr_leds, apa102_0_sck, apa102_0_mosi);
    apa102_1 = apa102_init(apa102_nbr_leds, apa102_1_sck, apa102_1_mosi);
    apa102_clear(apa102_0);
    apa102_clear(apa102_1);

    apa102_led_t green = { .a = 32, .r = 0, .g = 255, .b = 0 };
    apa102_setcolor(apa102_0, &green);
    apa102_setcolor(apa102_1, &green);
    apa102_send(apa102_0);
    apa102_send(apa102_1);
}

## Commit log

2016-09-02 Pre rev0.1, layout almost complete
2016-09-03 Changed to angled switch
2016-09-03 Moved switch
2016-09-03 Router all APA102 signal traces
2016-09-03 Route APA102 VIN traces
2016-09-03 Small PMIC tweaks
2016-09-03 Reorganized SWO signals
2016-09-16 Router some APA102 GND traces
2016-09-20 Renamed README
2016-09-20 Removed cp2102 IC
2016-09-20 Added GND/VIN copper pour
2016-09-20 Made trace nicer
2016-09-20 Moved traces out of the way from antennas
2016-09-20 Renamed battery holder to BAT
2016-10-02 hw_0.1
2016-10-02 Updated render
2016-12-30 Added to TODO
2016-12-30 Updated HW
2016-12-30 Added some components
2017-02-05 Add +/- and add missing copper pads
2017-02-05 Added 16340 battery holder
2017-02-05 Removed ALL tracks
2017-02-05 Increase MIC hole size
2017-02-05 Increased MIC pad sizes
2017-02-06 Add small v0.2 outline
2017-02-06 Removed 72 LEDs
2017-02-06 Longer pads on bno055
2017-02-06 Power, add pulldown to bq24075 EN1
2017-02-06 Misc?
2017-02-06 Power, add pulldown to bq24075 SYSOFF
2017-02-06 Added SIP32408 datasheet
2017-02-14 Added sip32408 footprint
2017-02-14 Shrunk led count in apa102 sub schematic
2017-02-14 Added sip32408 ic
2017-02-14 Switched to fat small design
2017-02-14 Add two missing 3d models
2017-02-19 Added mode button
2017-02-19 Fixed broken inductor schematic
2017-02-19 Change net name from VCHG to VREG
2017-02-19 Fixed SIP32408 footprint pins/pads lacking GND
2017-02-19 Started routing v0.2
2017-02-20 Started routing v0.2..
2017-02-20 Fixed APA102 bank 1 SPI trace names
2017-02-20 Started routing v0.2...
2017-02-20 Finished routing for v0.2
2017-02-20 Improved routing for v0.2
2017-02-20 Beefed up BAT USB GND traces
2017-02-21 Added bno055 datasheet
2017-02-21 Add pin1 indicator to bno055 footprint
2017-02-21 Add filled zones
2017-02-21 Add missing 3d model for bno055
2017-02-21 Generated v0.2 gerbers
2017-03-26 Started work on v0.3
2017-03-26 Add sip32408 dcm
2017-03-26 First draft of v0.3
2017-03-26 Change C9 footprint C0603->C0402
2017-03-26 Add v0.3 gerber zip
2017-05-05 Started adding fixes from v0.3 board
2017-05-12 Initial FW build environment import
2017-05-14 Add apa102 datasheet
2017-05-17 Add more issues to README
2017-06-13 Add firmware base
